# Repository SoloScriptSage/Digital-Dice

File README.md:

# 🎲 Digital Dice

A hardware random number generator built entirely from discrete logic ICs — no microcontroller, no code. Press the button, get a random number from 1 to 6 on a 7-segment display.

---

## How It Works

The circuit is split into four sections:

```
[Power Supply] → [555 Timer Oscillator] → [74LS90 Counter] → [74LS47 BCD Decoder] → [7-Segment Display]
```

**1. Power Supply (LM7805)**
Accepts any DC input (7–35V via barrel jack) and regulates it down to a stable 5V. Decoupling capacitors filter noise on the supply line.

**2. Clock Generator (NE555 in astable mode)**
The 555 timer oscillates continuously, generating a fast clock signal. While the button is not pressed, the counter increments at high speed — too fast for the eye to track, which creates the randomness.

**3. Counter / Random Number Generator (74LS90)**
A 4-bit BCD counter that cycles 0→9. A NAND gate feedback loop (74LS11) resets it at 6, so it only counts 0–5 (displayed as 1–6). When the button is released, the counter freezes at whatever value it landed on.

**4. BCD Decoder + Display (74LS47 + SC39-11EWA)**
The 74LS47 converts the binary counter output into the 7 segment drive signals. A 220Ω current-limiting resistor protects the display segments.

---

## Components

| Component | Part | Purpose |
|-----------|------|---------|
| U1 | NE555D | Astable oscillator (clock) |
| U2 | 74LS90 | 4-bit BCD counter |
| U3 | 74LS47 | BCD to 7-segment decoder |
| U4 | SC39-11EWA | Common cathode 7-segment display |
| U5 | LM7805 | 5V linear voltage regulator |
| U6A/D | 74LS11 | Triple 3-input AND gate (reset logic) |
| SW1 | SPST | Roll button |
| SW2 | SPST | Power switch |
| R1 | 10kΩ | 555 timing resistor |
| R5 | 220Ω | Display current limiter |
| R10 | 100kΩ | 555 timing resistor |
| J1 | Barrel Jack | DC power input |

---

## Schematic

Designed in **KiCad 9.0.2**. Full schematic and PCB layout files included in the repository.

---

## What I Learned

- Astable 555 timer configuration and RC timing calculations
- 4-bit BCD counter operation and modulo-N reset using gate feedback
- BCD to 7-segment decoding without a microcontroller
- PCB layout for mixed digital/analog circuits in KiCad

---

## Author

**Vladyslav Hirchuk** — [GitHub](https://github.com/SoloScriptSage) · [LinkedIn](https://linkedin.com/in/vladyslavhirchuk)

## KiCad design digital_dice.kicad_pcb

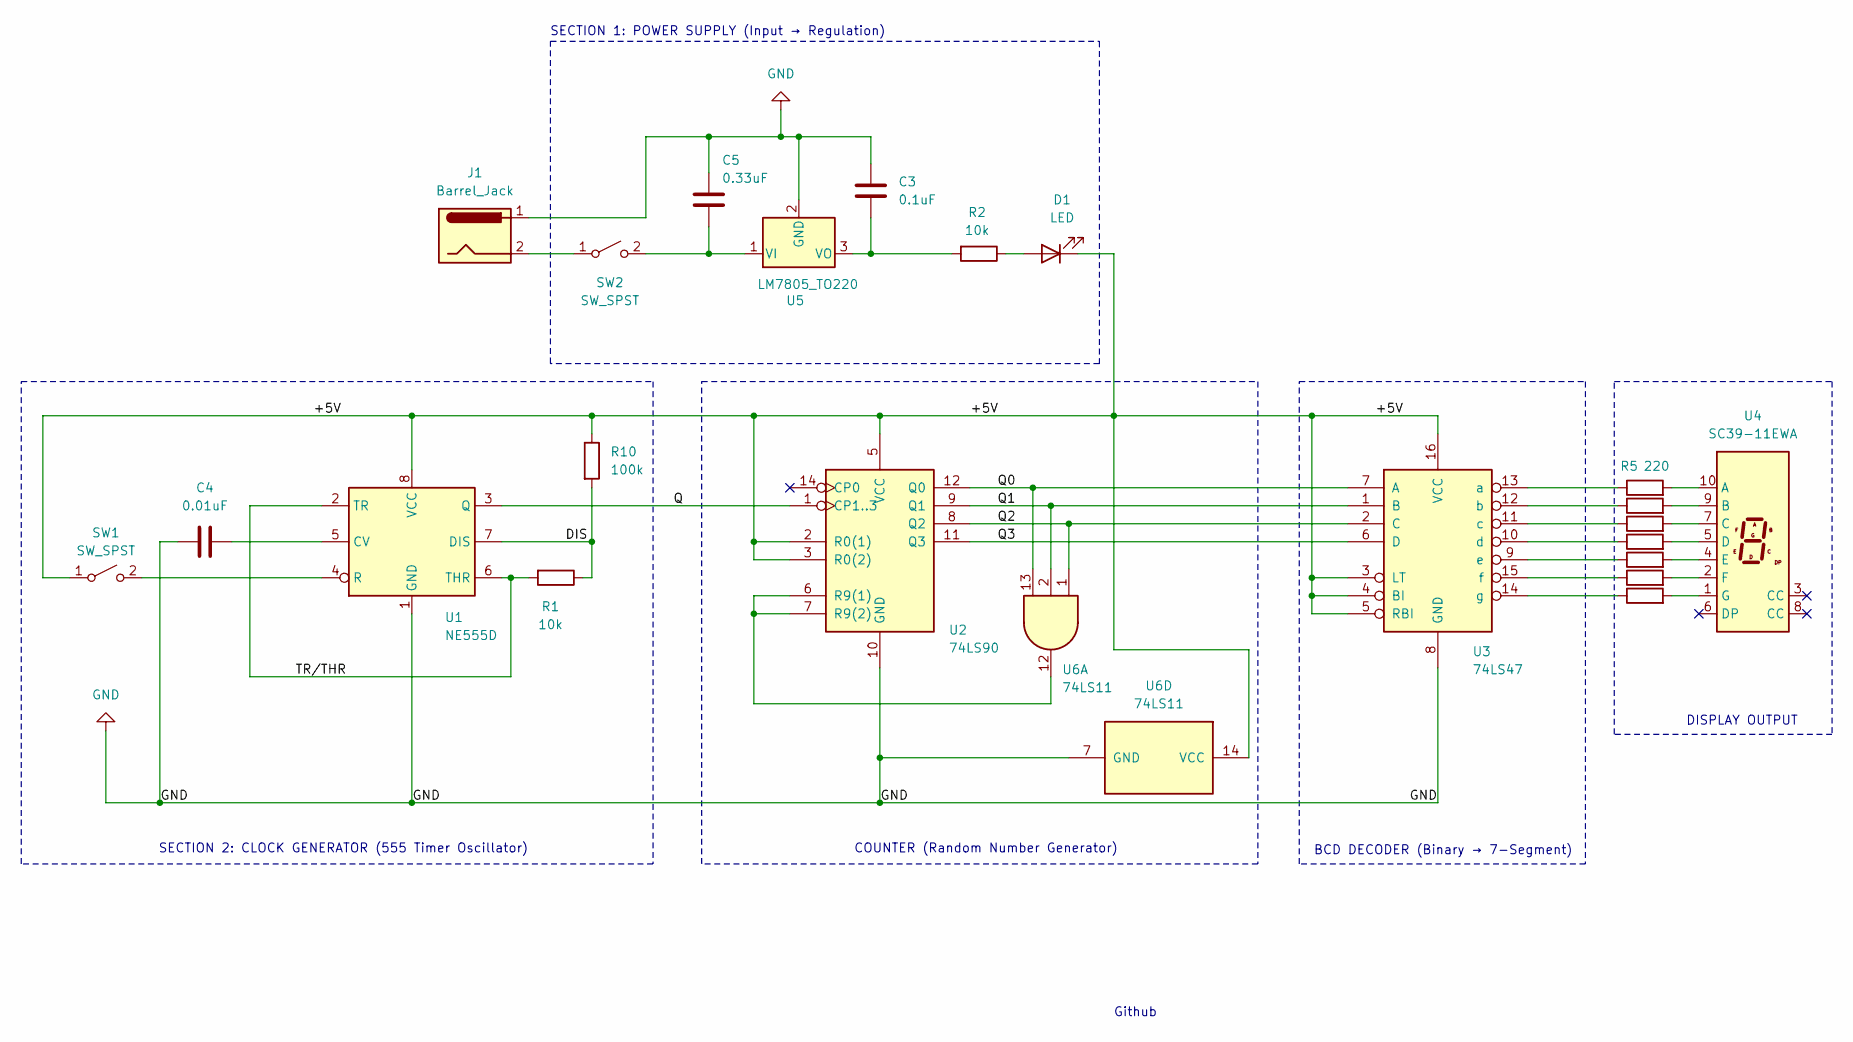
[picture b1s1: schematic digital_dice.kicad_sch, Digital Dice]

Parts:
C3: 0.1uF; C_Disc_D3.0mm_W1.6mm_P2.50mm
C4: 0.01uF; C_Disc_D3.0mm_W1.6mm_P2.50mm
C5: 0.33uF; C_Disc_D5.0mm_W2.5mm_P5.00mm
D1: LED; LED_D5.0mm
J1: Barrel_Jack; BarrelJack_Horizontal
R1, R2: 10k; R_Axial_DIN0207_L6.3mm_D2.5mm_P7.62mm_Horizontal
R3, R4, R5, R6, R7, R8, R9: 220; R_Axial_DIN0207_L6.3mm_D2.5mm_P7.62mm_Horizontal
R10: 100k; R_Axial_DIN0207_L6.3mm_D2.5mm_P7.62mm_Horizontal
SW1, SW2: SW_SPST; SW_PUSH_6mm
U1: NE555D; SOIC-8_3.9x4.9mm_P1.27mm
U2: 74LS90; DIP-14_W7.62mm_Socket
U3: 74LS47; DIP-16_W7.62mm_Socket
U4: SC39-11EWA; Sx39-1xxxxx
U5: LM7805_TO220; TO-220-3_Vertical
U6: 74LS11; DIP-14_W7.62mm_Socket

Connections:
/+5V: D1.1 (K), R10.1, SW1.1 (A), U1.8 (VCC), U2.2 (R0(1)), U2.3 (R0(2)), U2.5 (VCC), U3.3 (LT), U3.4 (BI), U3.5 (RBI), U3.16 (VCC), U6.14 (VCC)
/DIS: R1.1, R10.2, U1.7 (DIS)
/Q: U1.3 (Q), U2.1 (CP1..3)
/Q0: U2.12 (Q0), U3.7 (A), U6.13
/Q1: U2.9 (Q1), U3.1 (B), U6.2
/Q2: U2.8 (Q2), U3.2 (C), U6.1
/Q3: U2.11 (Q3), U3.6 (D)
/TR/THR: R1.2, U1.2 (TR), U1.6 (THR)
GND: C3.1, C4.1, C5.1, J1.1, U1.1 (GND), U2.10 (GND), U3.8 (GND), U5.2 (GND), U6.7 (GND)
unnamed: D1.2 (A), R2.1
unnamed: SW1.2 (B), U1.4 (R)
unnamed: J1.2, SW2.1 (A)
unnamed: C5.2, SW2.2 (B), U5.1 (VI)
unnamed: C4.2, U1.5 (CV)
unnamed: U2.6 (R9(1)), U2.7 (R9(2)), U6.12
unnamed: R5.1, U3.13 (a)
unnamed: R3.1, U3.12 (b)
unnamed: R4.1, U3.11 (c)
unnamed: R6.1, U3.10 (d)
unnamed: R7.1, U3.9 (e)
unnamed: R8.1, U3.15 (f)
unnamed: R9.1, U3.14 (g)
unnamed: R5.2, U4.10 (A)
unnamed: R3.2, U4.9 (B)
unnamed: R4.2, U4.7 (C)
unnamed: R6.2, U4.5 (D)
unnamed: R7.2, U4.4 (E)
unnamed: R8.2, U4.2 (F)
unnamed: R9.2, U4.1 (G)
unnamed: C3.2, R2.2, U5.3 (VO)

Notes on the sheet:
DISPLAY OUTPUT
BCD DECODER (Binary → 7-Segment)
SECTION 2: CLOCK GENERATOR (555 Timer Oscillator)
Github
COUNTER (Random Number Generator)
SECTION 1: POWER SUPPLY (Input → Regulation)

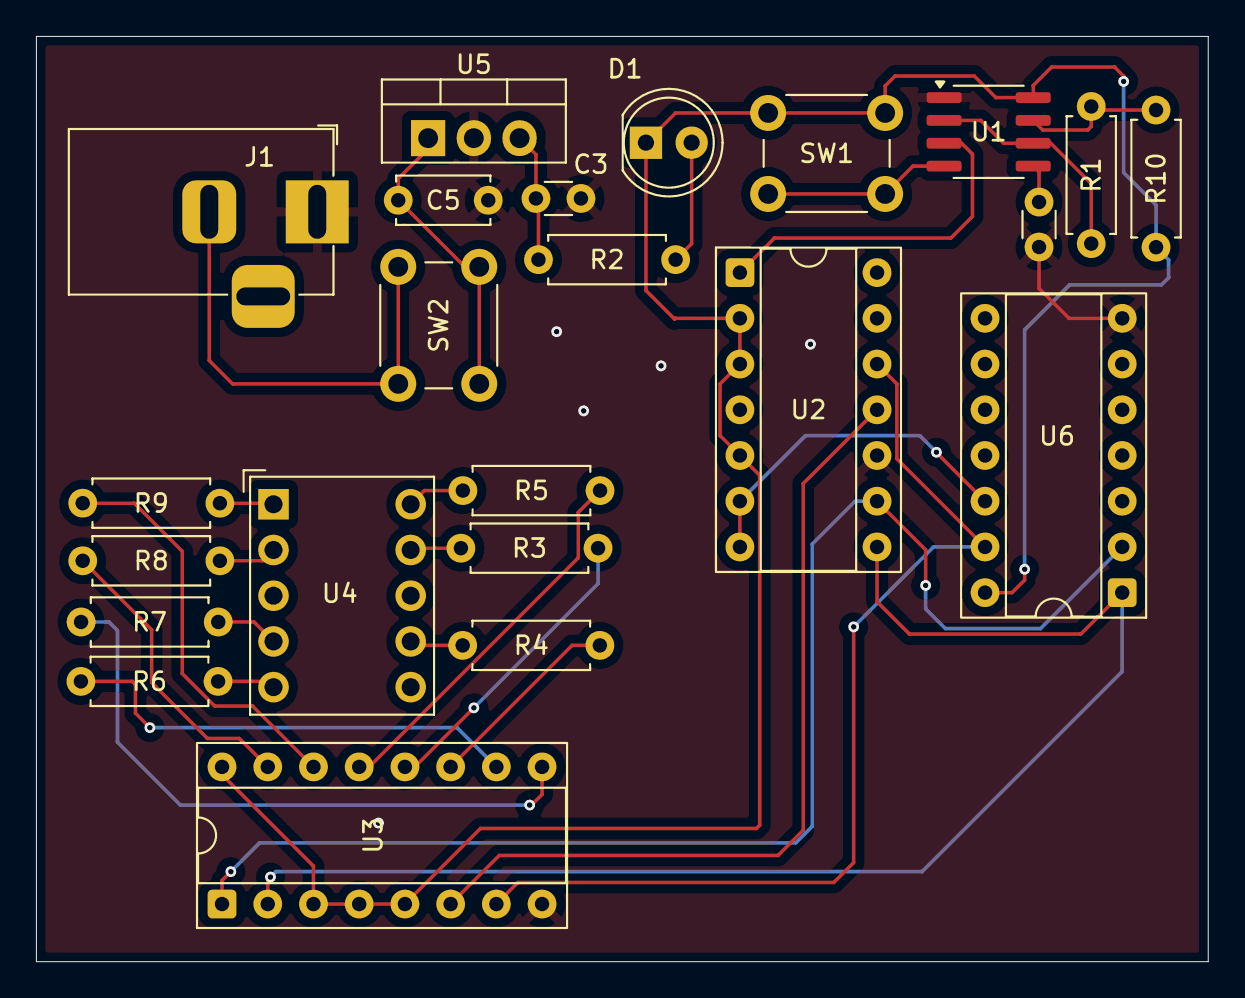
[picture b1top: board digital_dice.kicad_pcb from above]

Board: 2 copper layers, 65.1 x 51.4 mm, 23 parts (0 on the bottom side), 30 nets.

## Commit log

2025-11-08 Restructure: move project files to root directory
2025-11-09 Final Touches:
2025-11-09 GitIgnore
2025-11-09 Structure of the repo
2026-03-05 Update PCB layout
2026-03-05 Rewrite README with clean formatting
2026-03-05 Expand README with project details and author info
    Added detailed explanation of the digital dice project, including its components, how it works, and what was learned during the process.
